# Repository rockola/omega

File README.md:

# omega
FET treble booster by runoffgroove.com

1590A compatible, 9mm boardmount pots, SMD MMBF5457 JFET (=2N5457)

See [runoffgroove.com Omega page](http://runoffgroove.com/omega.html) for more info.

* v1.3-1: initial version

## LICENSE

Omega by [http://runoffgroove.com](runoffgroove.com) is licensed under the [Creative Commons Attribution-NonCommercial-ShareAlike 3.0 Unported License](https://creativecommons.org/licenses/by-nc-sa/3.0/).

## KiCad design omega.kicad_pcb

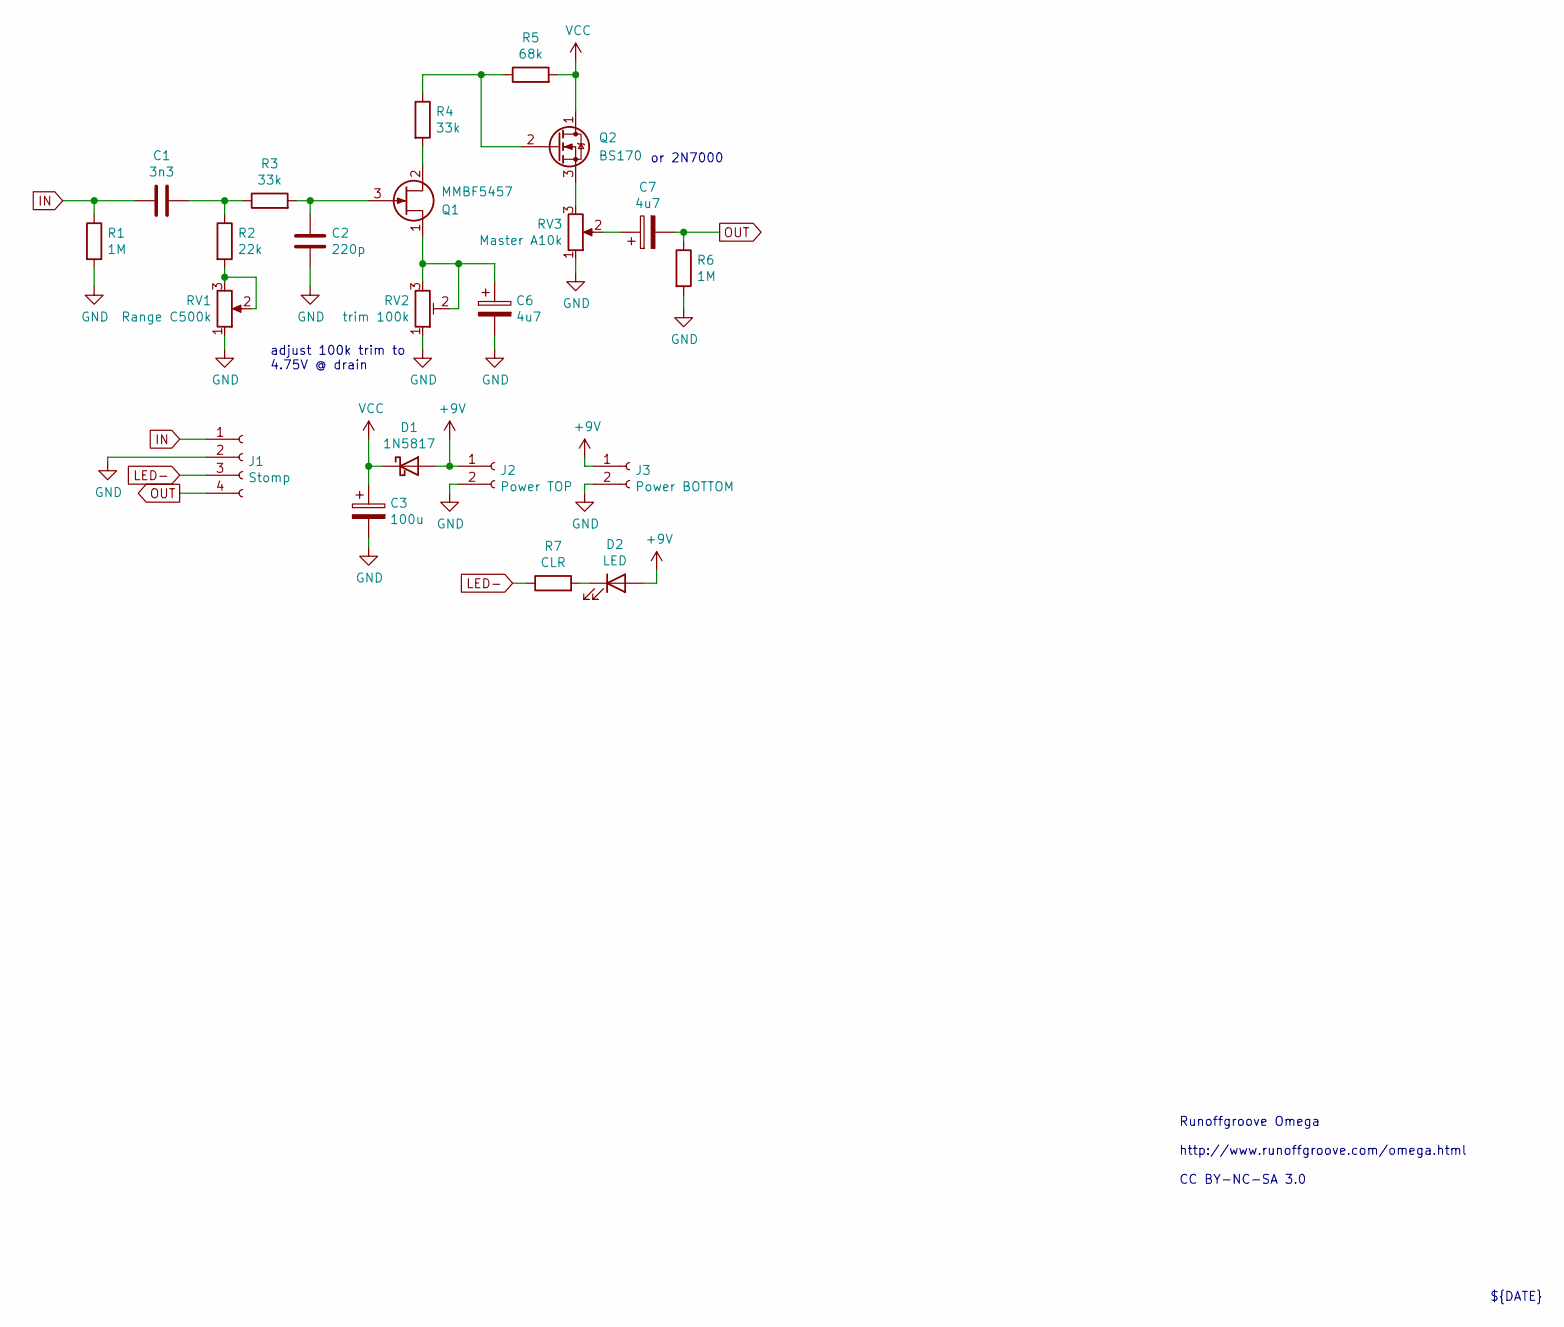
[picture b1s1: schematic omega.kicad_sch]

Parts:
C1: 3n3; C_Box_7.2_2.5
C2: 220p; 0.2_22.SML
C3: 100u; CP_D5.0_P2.50
C6, C7: 4u7; CP_D5.0_P2.50
D1: 1N5817; D_DO-41_SOD81_P10.16mm_Horizontal
D2: LED; LED.3mm
J1: Stomp; Stomp_4pin
J2: Power TOP; Power_Header_2pin_TOP
J3: Power BOTTOM; Power_Header_2pin
Q1: MMBF5457; SOT-23
Q2: BS170; TO92_DGS
R1, R6: 1M; R_DIN0207
R2: 22k; R_DIN0207
R3, R4: 33k; R_DIN0207
R5: 68k; R_DIN0207
R7: CLR; R_DIN0207
RV1: Range C500k; 9MM_METAL_SHAFT
RV2: trim 100k; TRIM1
RV3: Master A10k; 9MM_METAL_SHAFT

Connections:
+9V: D1.2 (A), D2.2 (A), J2.1, J3.1
GND: C2.2, C3.2, C6.2, J1.2, J2.2, J3.2, R1.2, R6.2, RV1.1, RV2.1, RV3.1
IN: C1.1, J1.1, R1.1
LED-: J1.3, R7.1
unnamed: C1.2, R2.1, R3.1
unnamed: C2.1, Q1.3 (G), R3.2
unnamed: C6.1, Q1.1 (D), RV2.2, RV2.3
unnamed: C7.1, RV3.2
unnamed: D2.1 (K), R7.2
unnamed: Q1.2 (S), R4.2
unnamed: Q2.2 (G), R4.1, R5.1
unnamed: Q2.3 (S), RV3.3
unnamed: R2.2, RV1.2, RV1.3
OUT: C7.2, J1.4, R6.1
VCC: C3.1, D1.1 (K), Q2.1 (D), R5.2

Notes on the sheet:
${TITLE}
adjust 100k trim to 4.75V @ drain
or 2N7000
${DATE}
Runoffgroove Omega http://www.runoffgroove.com/omega.html CC BY-NC-SA 3.0
${REVISION}

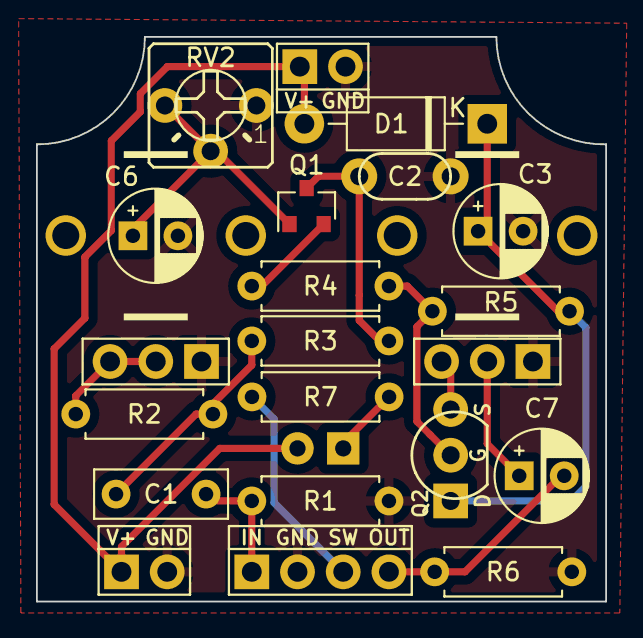
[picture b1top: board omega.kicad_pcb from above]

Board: 2 copper layers, 31.6 x 31.4 mm, 22 parts (1 on the bottom side), 15 nets.

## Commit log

2020-09-23 v1.3-1 initial version
2020-09-23 added runoffgroove.com attribution to back silkscreen
2020-09-24 tighter visual layout, same functionality
2022-01-11 updated to KiCad 6.0
